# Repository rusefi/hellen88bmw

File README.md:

# Team

Product Owner @StefanSt

[Issue Tracker](https://github.com/rusefi/hellen88bmw-issues)

[User documentation](https://rusefi.com/s/hellen88bmw)

Part of https://github.com/andreika-git/hellen-one family

Inspired by https://github.com/rusefi/hw_88_bmw

# compatible cases

0260002360 TCU yes or no?

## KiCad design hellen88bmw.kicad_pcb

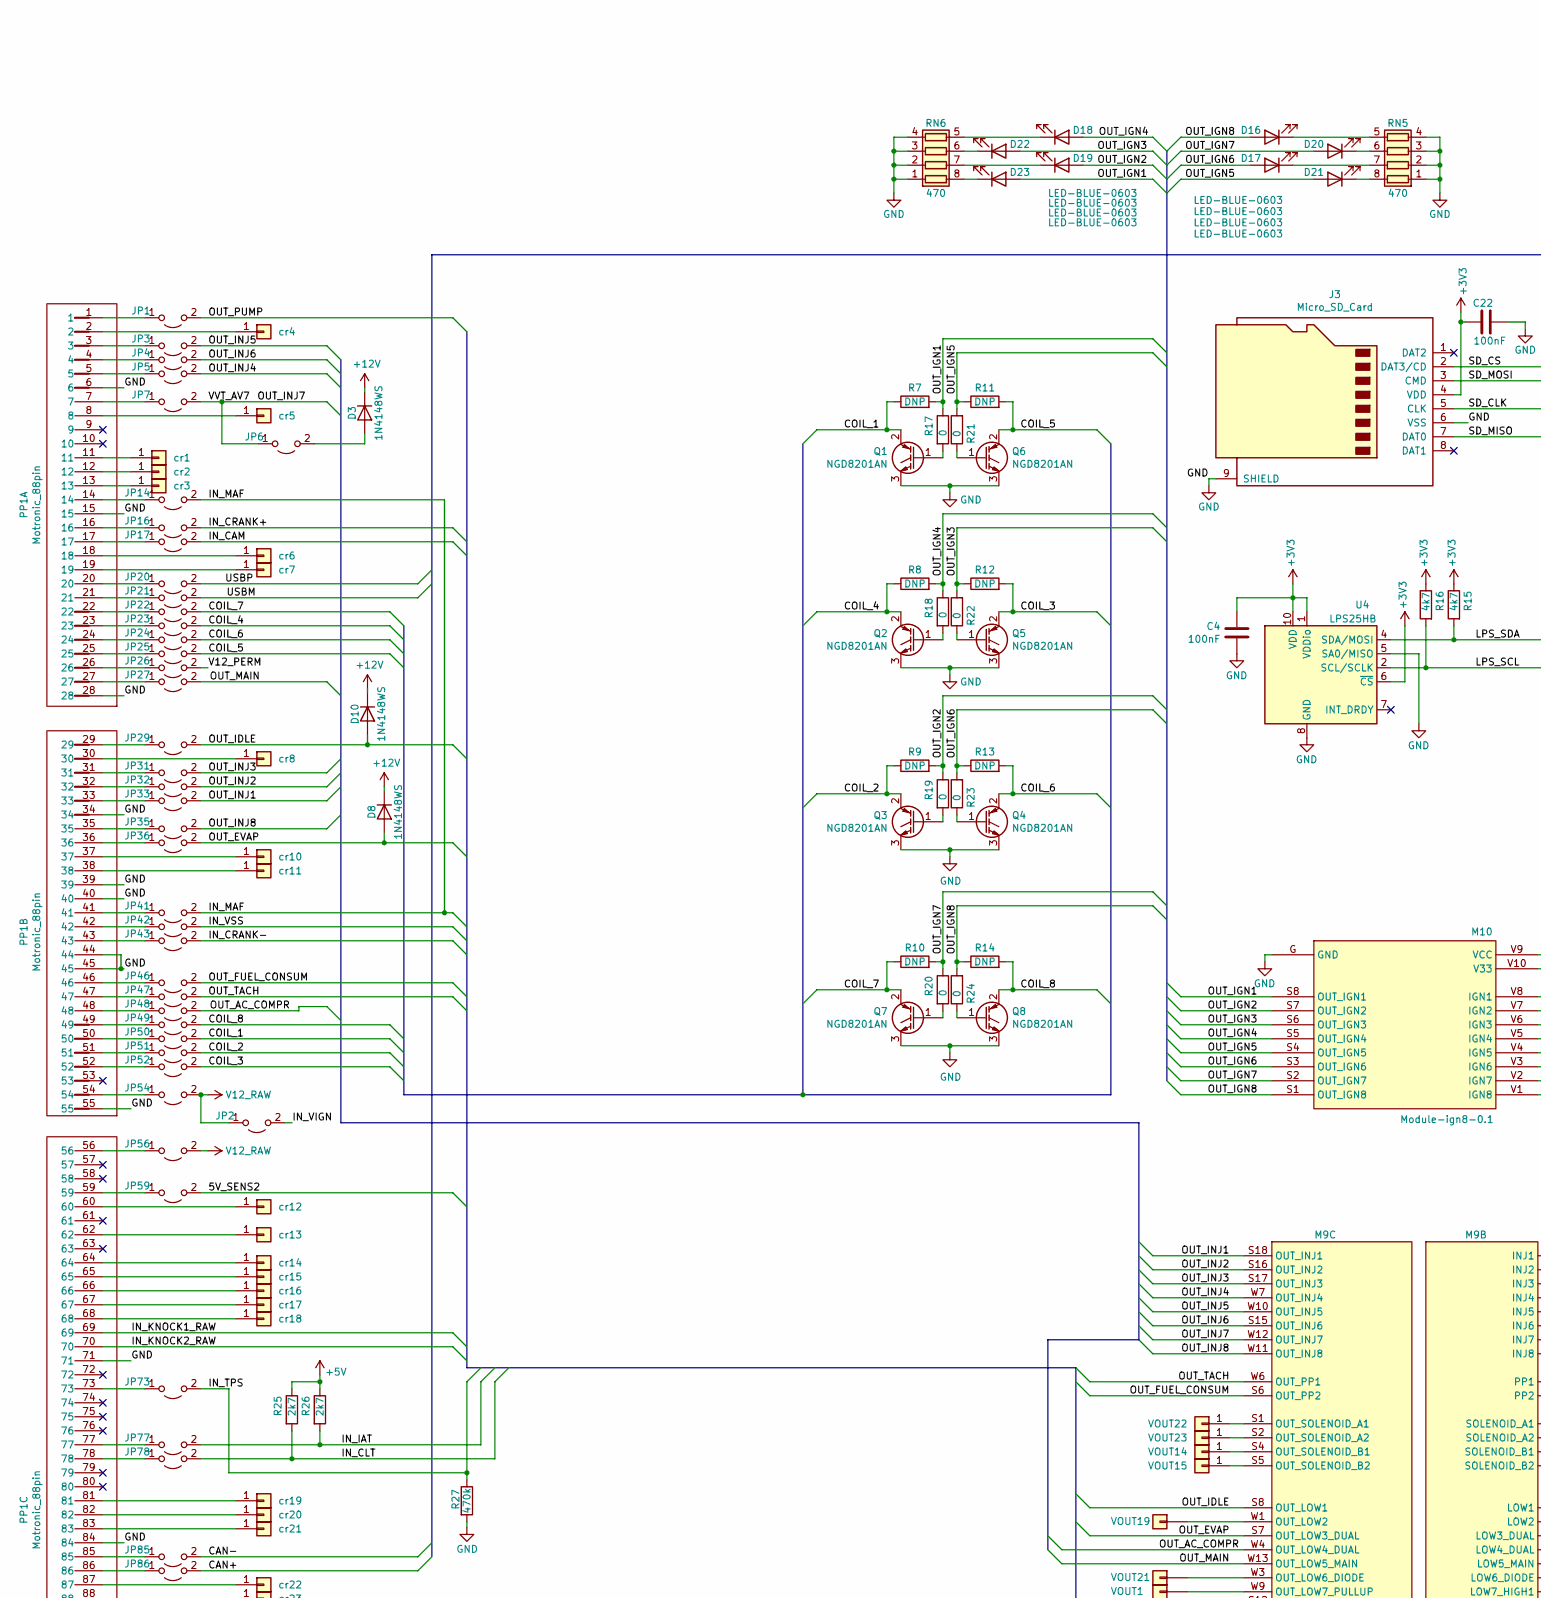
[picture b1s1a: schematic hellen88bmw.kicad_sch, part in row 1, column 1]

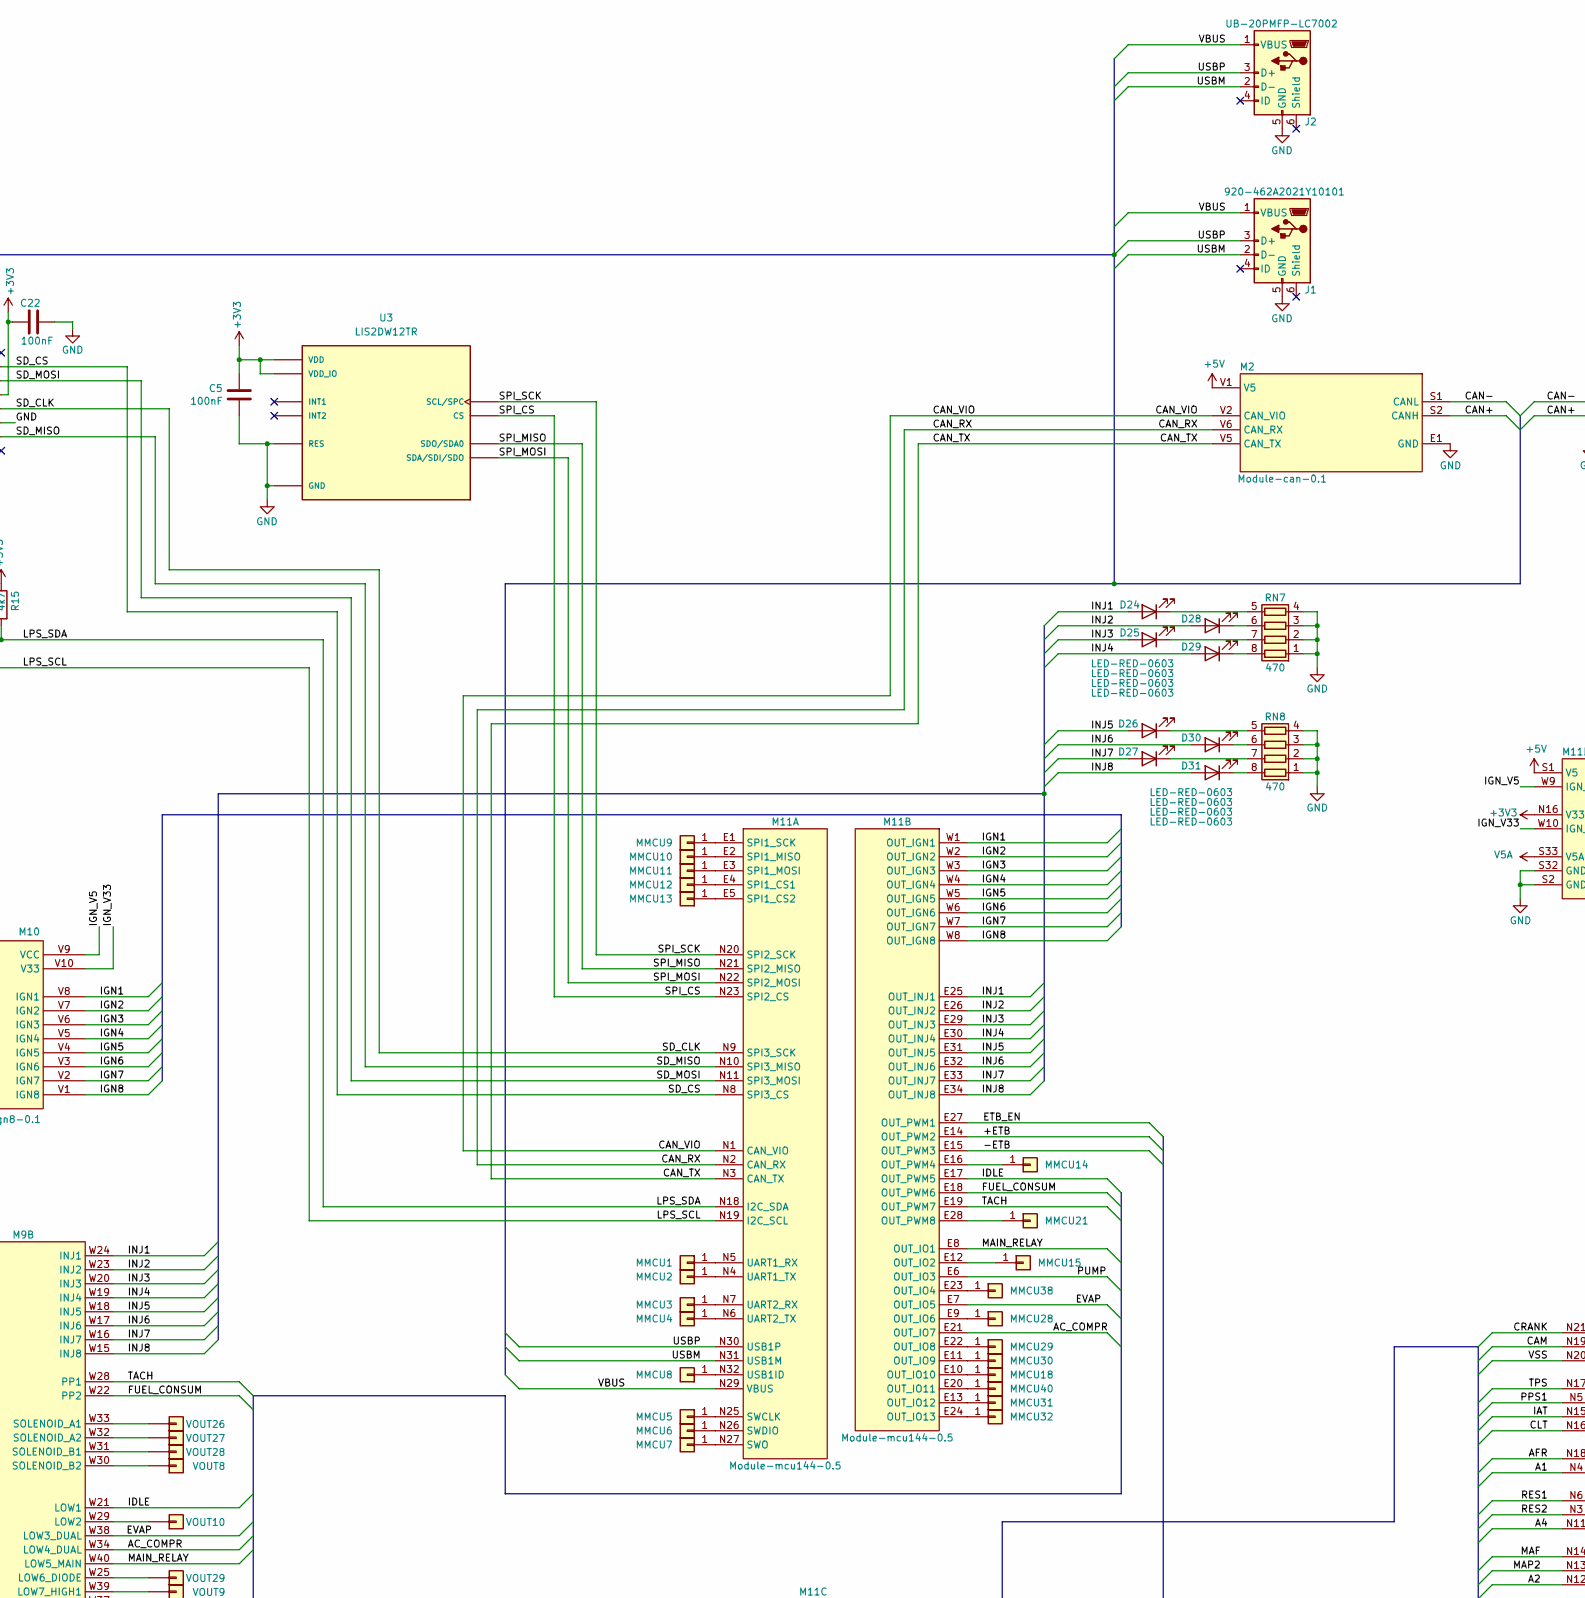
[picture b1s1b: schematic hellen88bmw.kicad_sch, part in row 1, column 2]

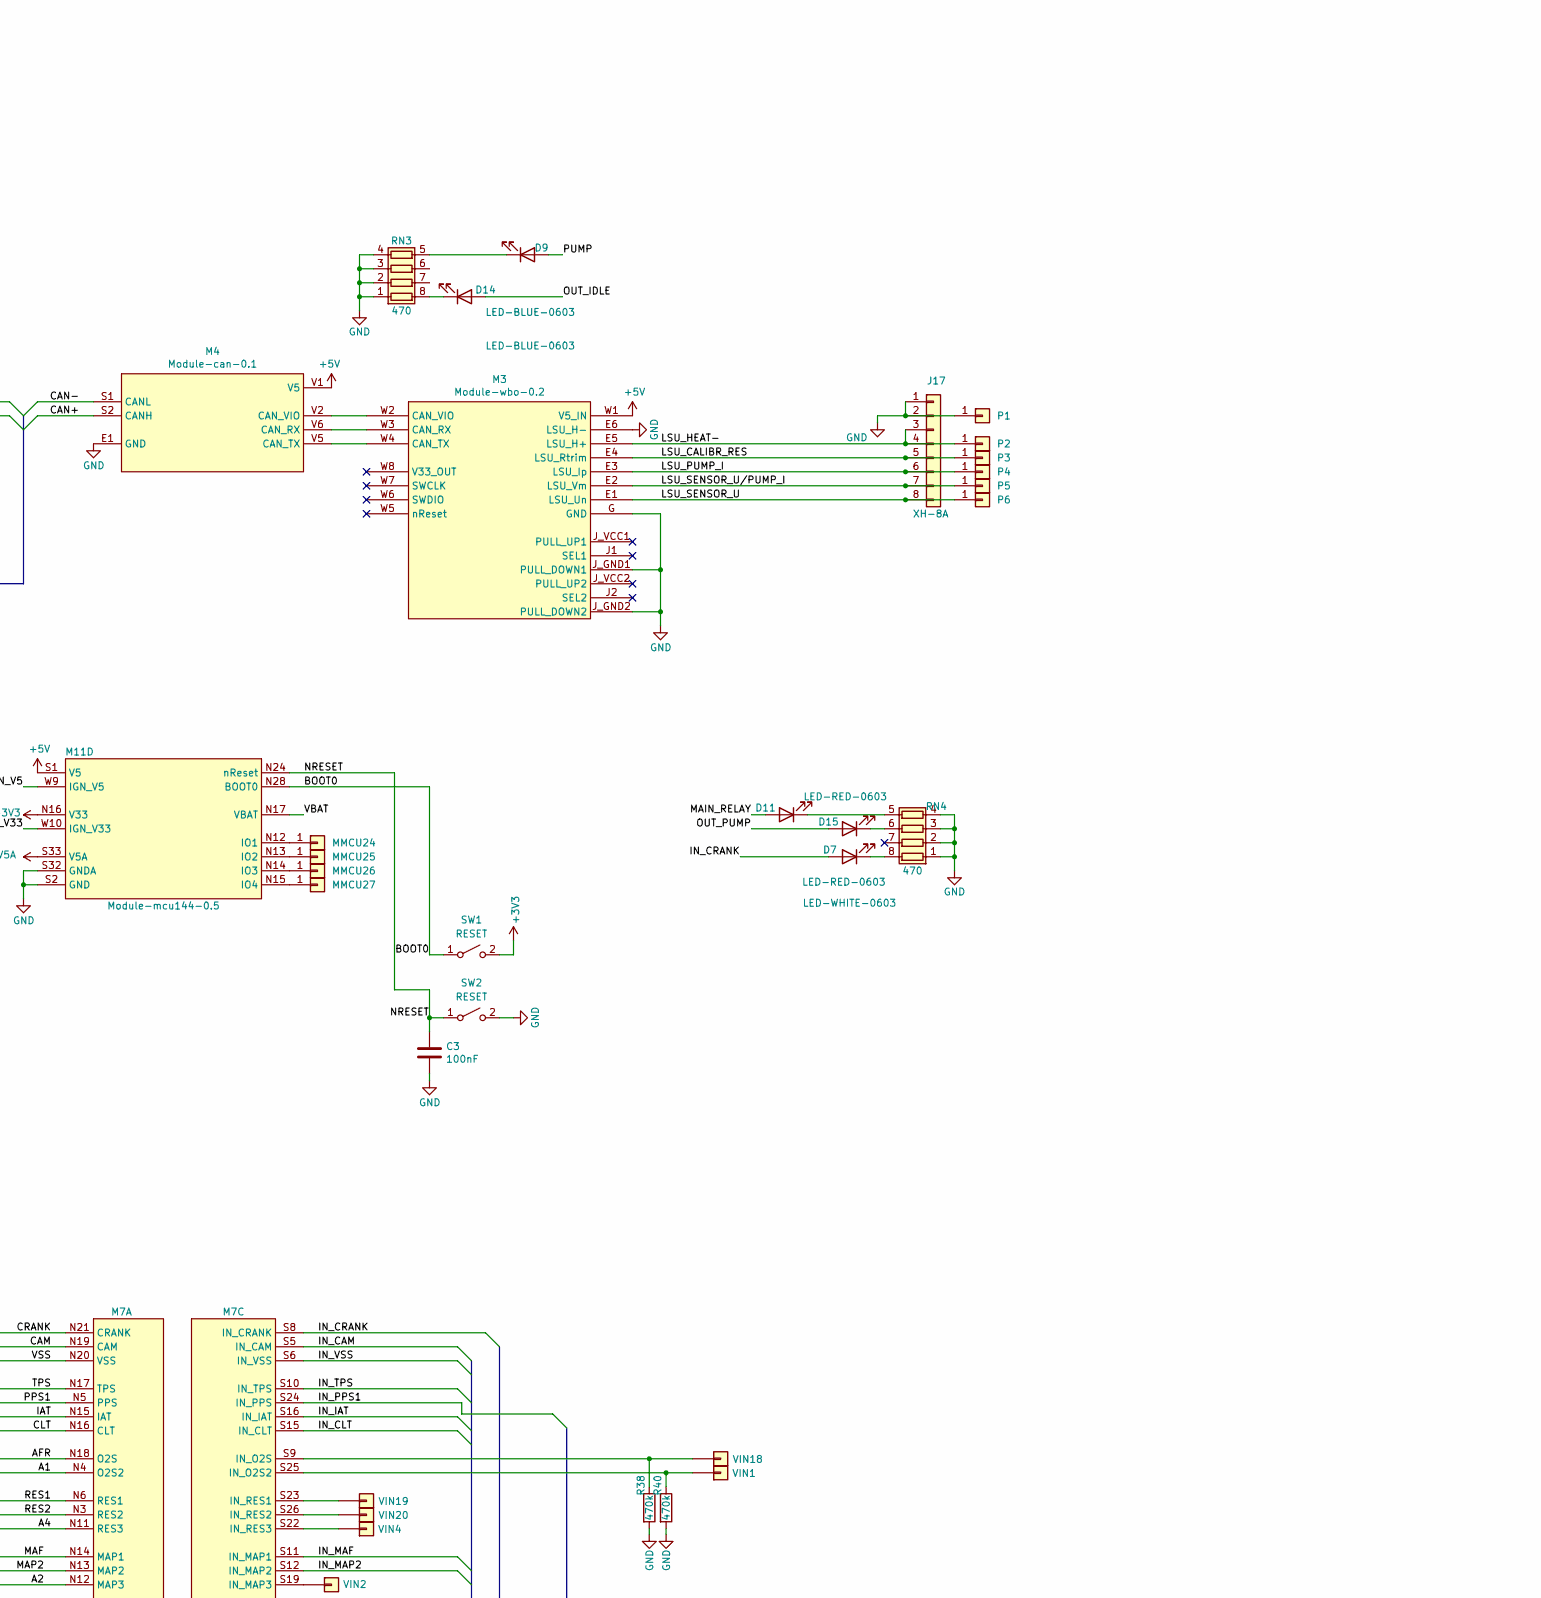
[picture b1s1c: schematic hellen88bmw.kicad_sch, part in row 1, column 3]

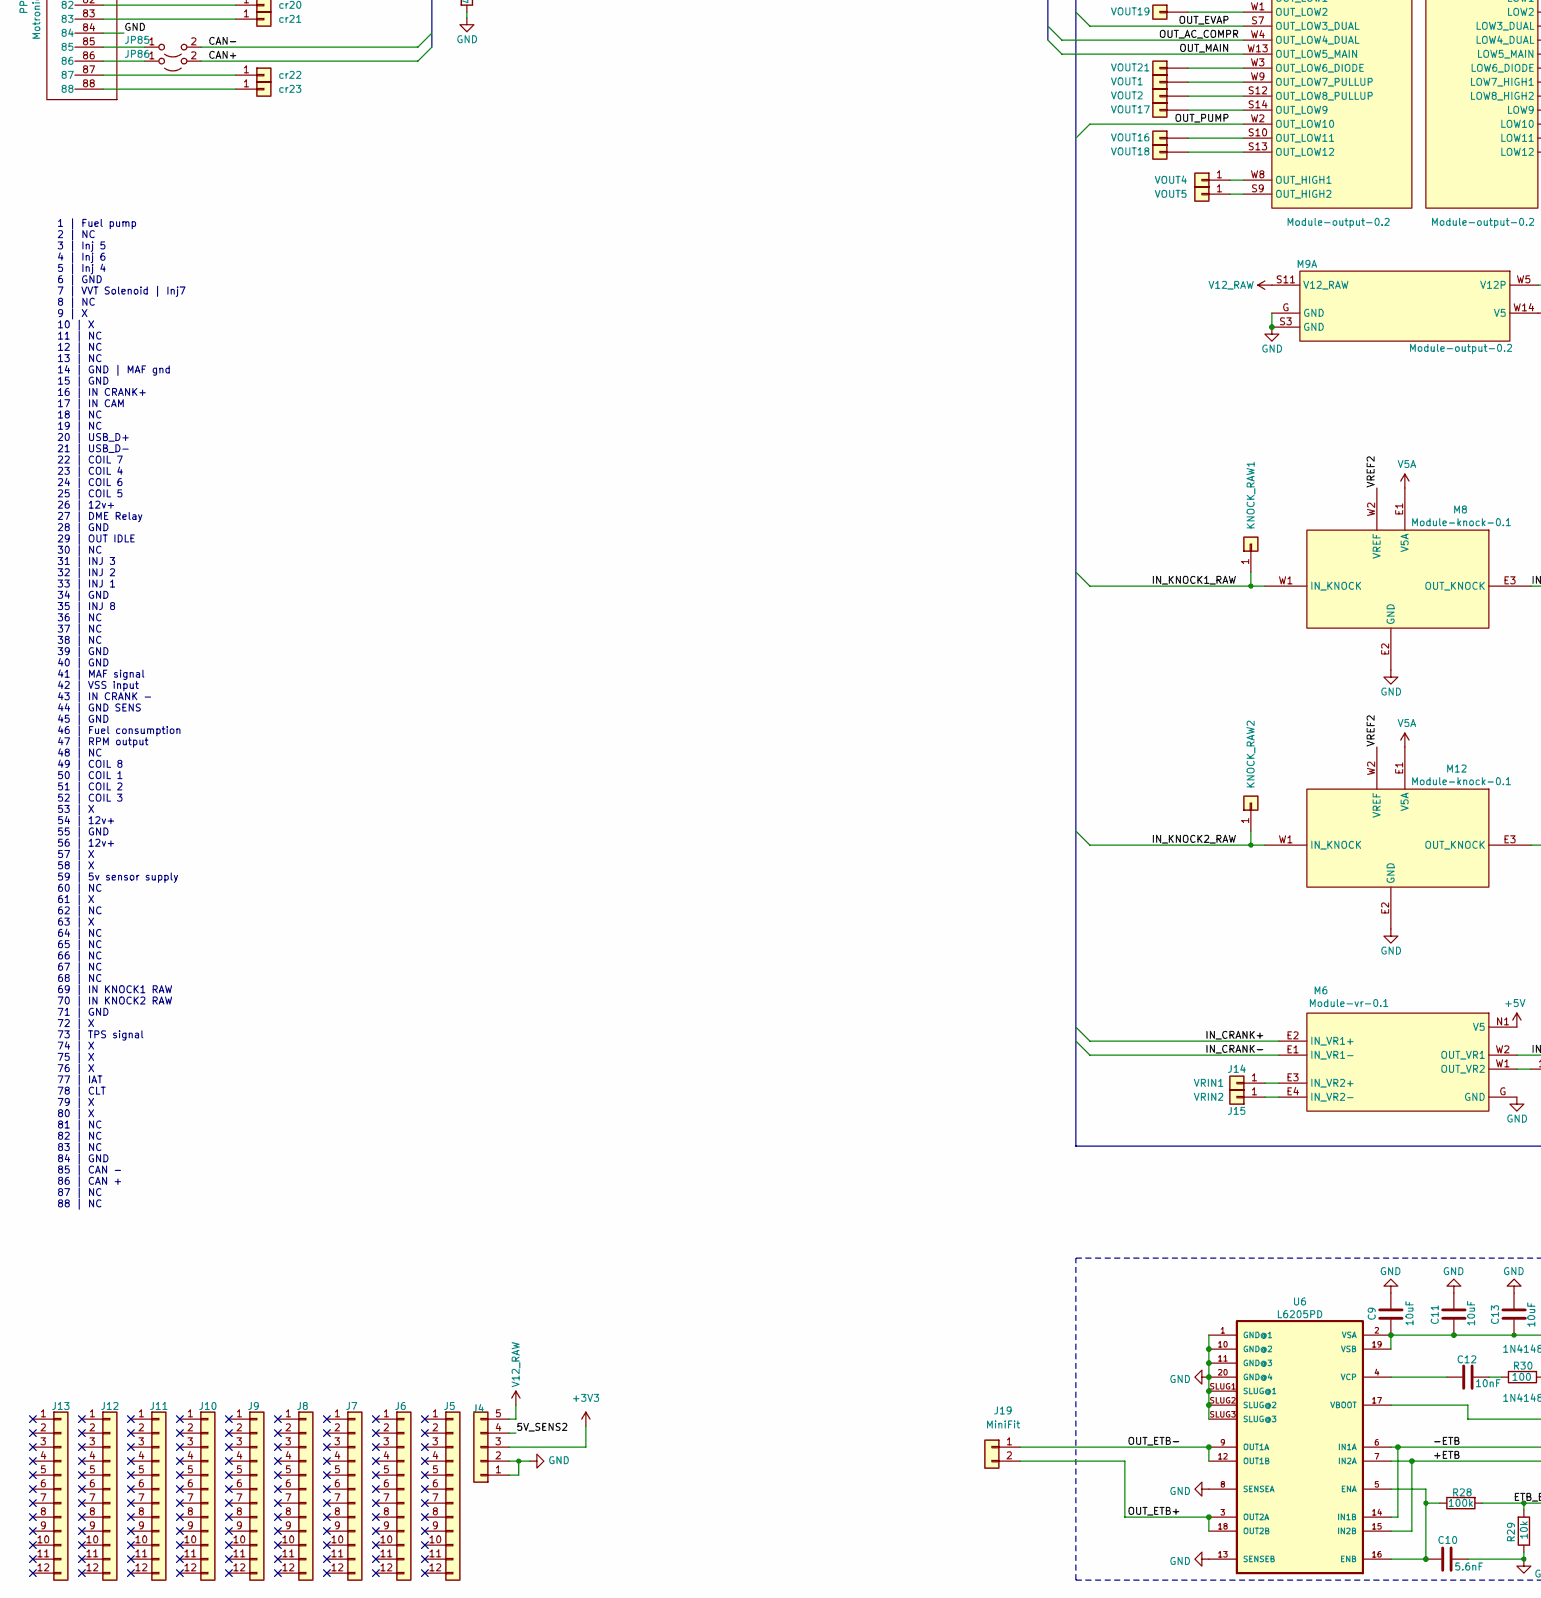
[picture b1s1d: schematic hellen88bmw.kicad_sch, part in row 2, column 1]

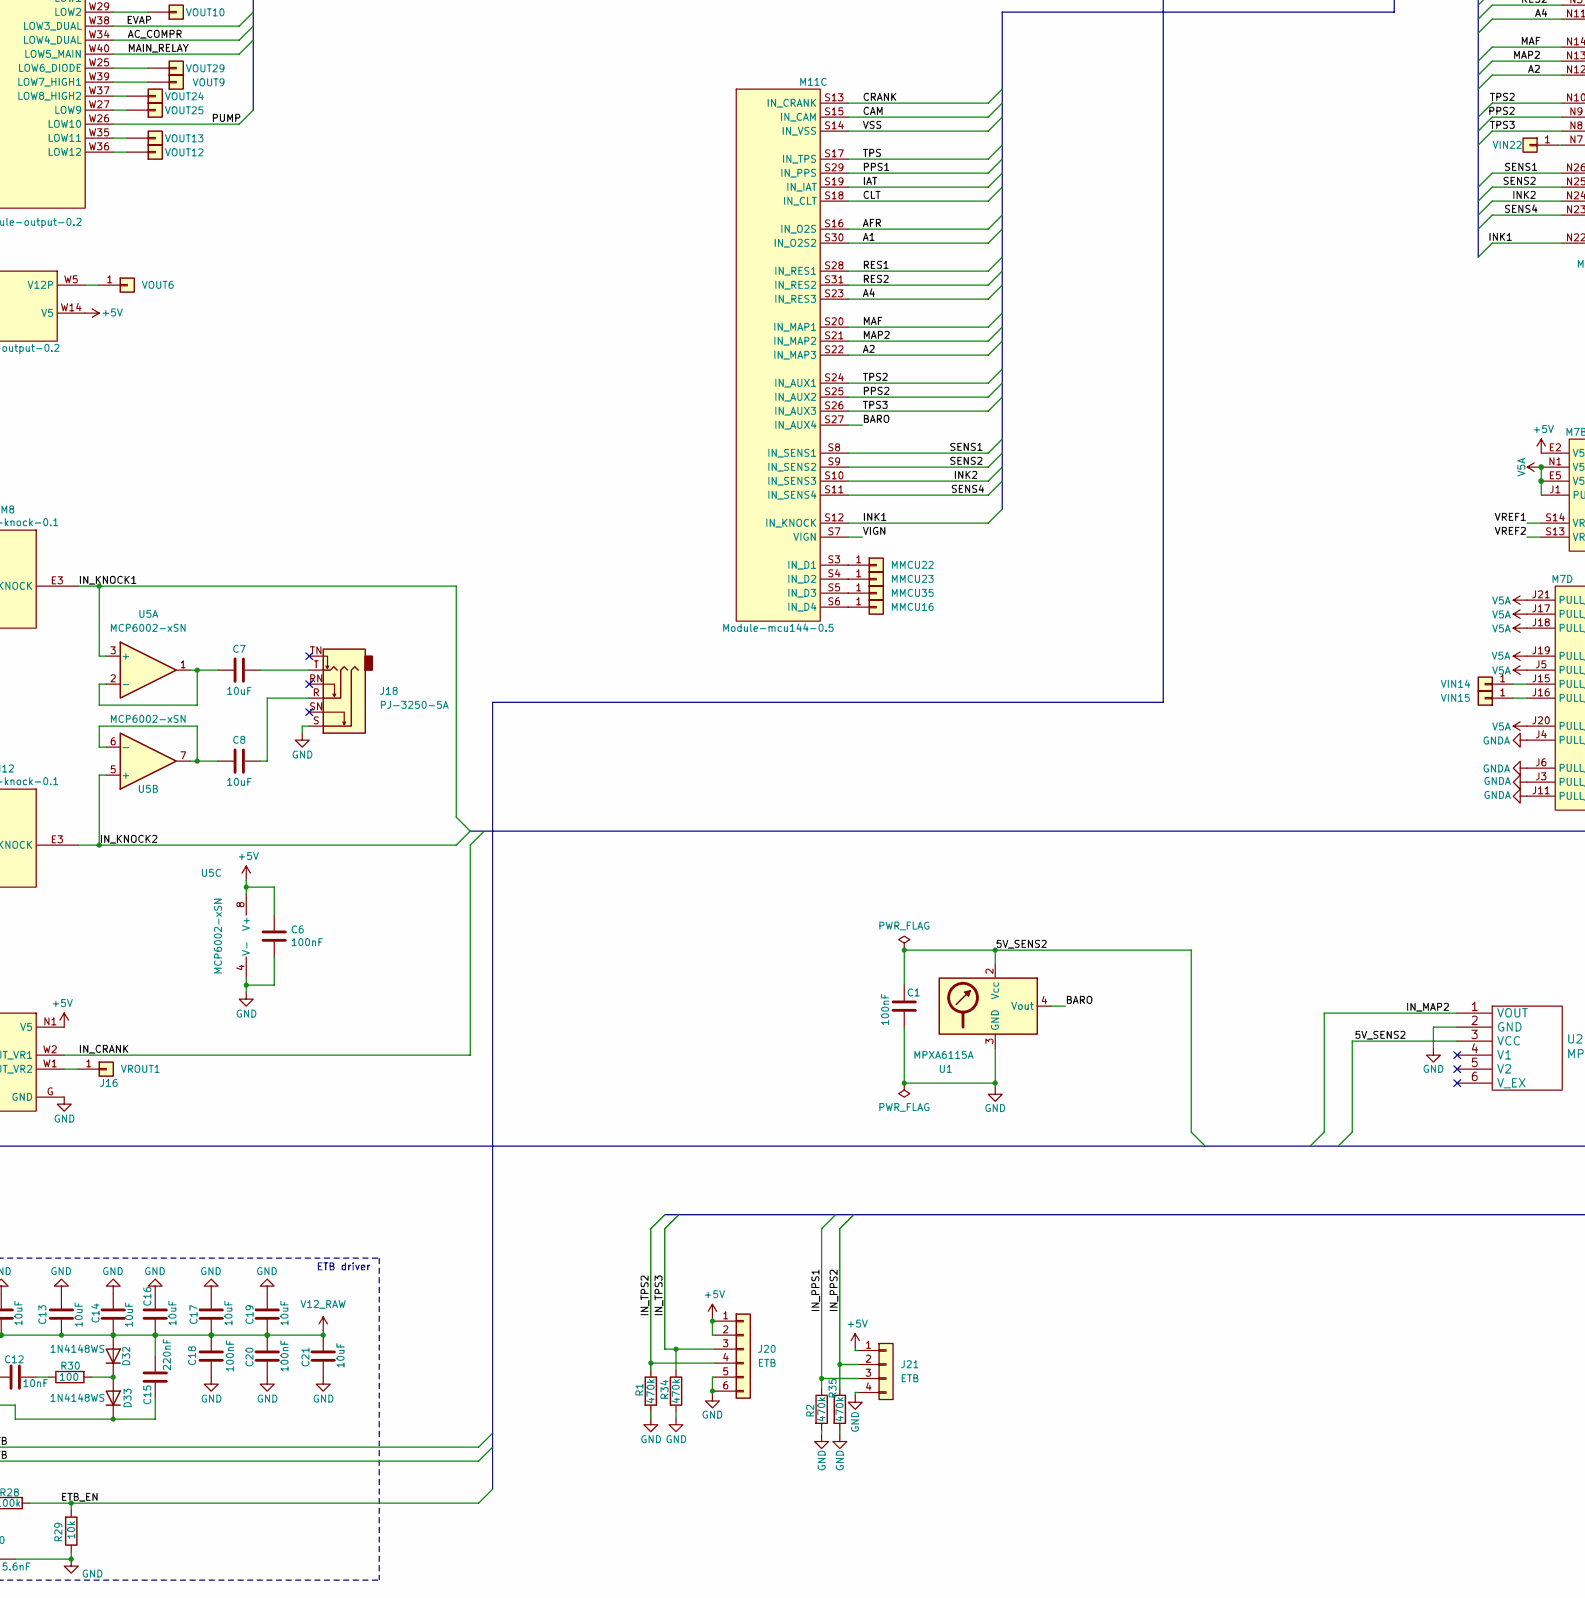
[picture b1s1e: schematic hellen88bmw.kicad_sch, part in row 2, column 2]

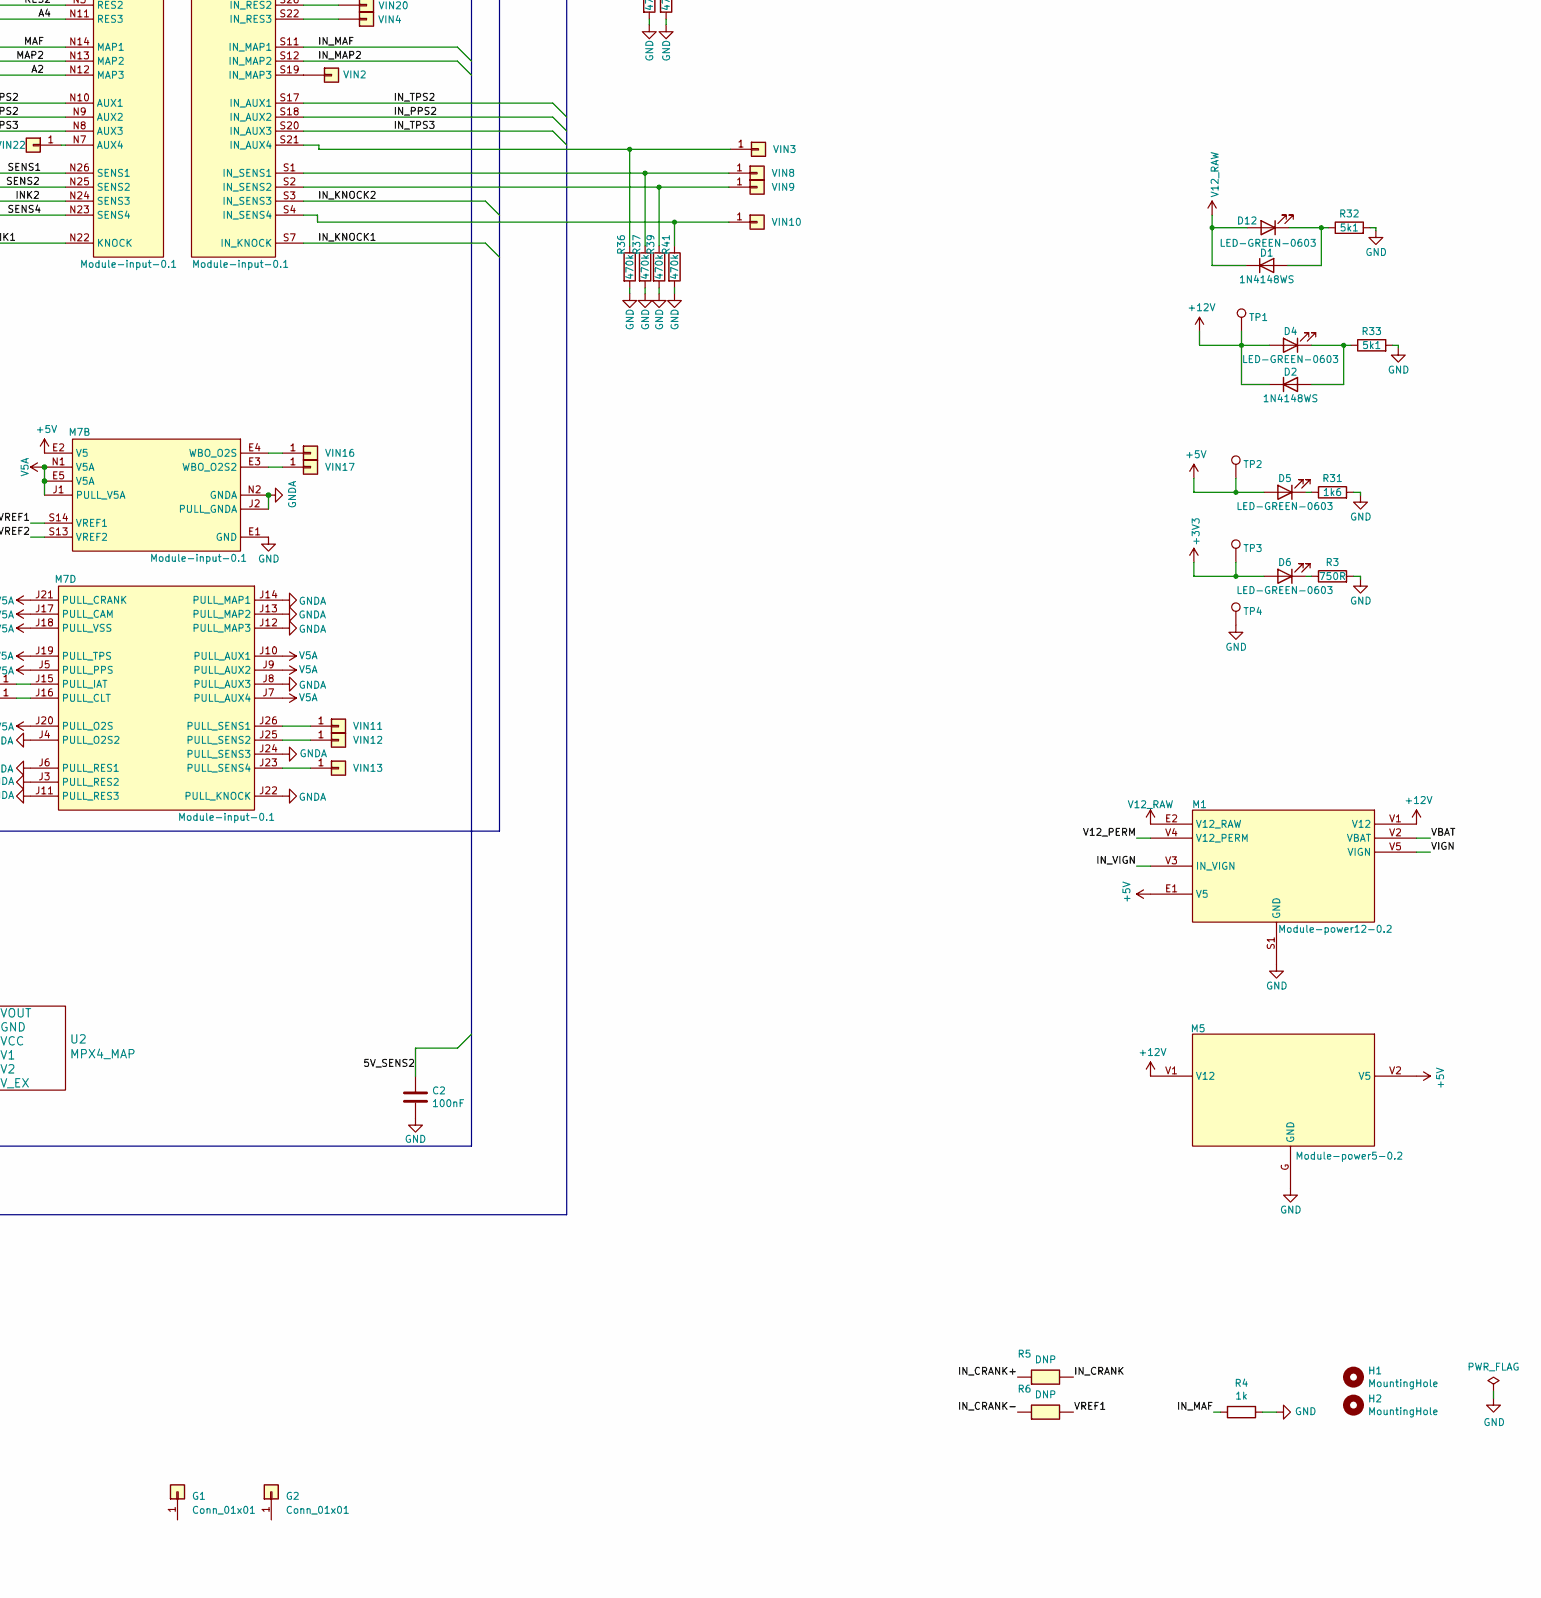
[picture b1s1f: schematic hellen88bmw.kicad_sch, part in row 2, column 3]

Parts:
C1, C2, C3, C4, C5, C6, C18, C20, C22: 100nF; C_0402_1005Metric; LCSC C105882
C7, C8, C9, C11, C13, C14, C16, C17, C19, C21: 10uF; C_0603_1608Metric; LCSC C87152
C10: 5.6nF; C_0402_1005Metric; LCSC C115688
C12: 10nF; C_0402_1005Metric; LCSC C541443
C15: 220nF; C_0402_1005Metric; LCSC C106258
D1, D2, D3, D8, D10, D32, D33: 1N4148WS; D_SOD-323; LCSC C2128
D4, D5, D6, D12: LED-GREEN-0603; LED_0603_1608Metric; LCSC C72043
D7: LED-WHITE-0603; LED_0603_1608Metric; LCSC C84265
D9, D14, D16, D17, D18, D19, D20, D21, D22, D23: LED-BLUE-0603; LED_0603_1608Metric; LCSC C72041
D11, D15, D24, D25, D26, D27, D28, D29, D30, D31: LED-RED-0603; LED_0603_1608Metric; LCSC C2286
G1, G2: Conn_01x01; LOGO
H1, H2: MountingHole; MountingHole_4.3mm_M4_DIN965
J1: 920-462A2021Y10101; USB-MINI-B-VERTICAL; LCSC C13453
J2: UB-20PMFP-LC7002; PinHeader_1x05_P2.00mm_Vertical; LCSC DNP
J3: Micro_SD_Card; 693072010801
J4: Conn_01x05; PinHeader_1x05_P2.54mm_Vertical
J5, J6, J7, J8, J9, J10, J11, J12, J13: Conn_01x12; PinHeader_1x12_P2.54mm_Vertical
J14: VRIN1; PinHeader_1x01_P1.00mm_Vertical
J15: VRIN2; PinHeader_1x01_P1.00mm_Vertical
J16: VROUT1; PinHeader_1x01_P1.00mm_Vertical
J17: XH-8A; LCSC C10385
J18: PJ-3250-5A; Jack_3.5mm_CUI_SJ1-3535NG_Horizontal; LCSC C165947
J19: MiniFit; Molex_Mini-Fit_Jr_5569-02A2_2x01_P4.20mm_Horizontal
J20: ETB; PinHeader_1x06_P2.54mm_Vertical; LCSC C343639
J21: ETB; PinHeader_1x04_P2.54mm_Vertical; LCSC C343639
JP1, JP2, JP3, JP4, JP5, JP7, JP14, JP16, JP17, JP22, JP23, JP24, JP25, JP26, JP27, JP29, JP31, JP32, JP33, JP35, JP36, JP41, JP42, JP43, JP46, JP47, JP48, JP49, JP50, JP51, JP52, JP56, JP59, JP73, JP77, JP78, JP85, JP86: Jumper_2_Open; SM0805_jumper; LCSC C17477
JP6, JP20, JP21, JP54: Jumper_2_Open; SM0805_jumper; LCSC DNP
KNOCK_RAW1: IN_KNOCK1_RAW; PinHeader_1x01_P1.00mm_Vertical
KNOCK_RAW2: IN_KNOCK2_RAW; PinHeader_1x01_P1.00mm_Vertical
M1: Module-power12-0.2; power12
M2, M4: Module-can-0.1; can
M3: Module-wbo-0.2; wbo
M5: Module-power5-0.2; power5
M6: Module-vr-0.1; vr
M7: Module-input-0.1; input
M8, M12: Module-knock-0.1; knock
M9: Module-output-0.2; output
M10: Module-ign8-0.1; ign8
M11: Module-mcu144-0.5; mcu
MMCU1, MMCU2, MMCU3, MMCU4, MMCU5, MMCU6, MMCU7, MMCU8, MMCU9, MMCU10, MMCU11, MMCU12, MMCU13, MMCU14, MMCU15, MMCU16, MMCU18, MMCU21, MMCU22, MMCU23, MMCU24, MMCU25, MMCU26, MMCU27, MMCU28, MMCU29, MMCU30, MMCU31, MMCU32, MMCU35, MMCU38, MMCU40: MMCU; PinHeader_1x01_P1.00mm_Vertical
P1, P2, P3, P4, P5, P6: P; Pin_D1.0mm_L10.0mm
PP1: Motronic_88pin; 88pin_STS
Q1, Q2, Q3, Q4, Q5, Q6, Q7, Q8: NGD8201AN; TO-252-2; LCSC C151649
R1, R2, R27, R34, R35, R36, R37, R38, R39, R40, R41: 470k; R_0402_1005Metric
R3: 750R; R_0402_1005Metric
R4: 1k; R_0402_1005Metric; LCSC C105637
R5, R6: DNP; R_0402_1005Metric; LCSC NA
R7, R8, R9, R10, R11, R12, R13, R14: DNP; R_2512_6332Metric; LCSC NA
R15, R16: 4k7; R_0402_1005Metric; LCSC C163826
R17, R18, R19, R20, R21, R22, R23, R24: 0; R_0402_1005Metric; LCSC C106231
R25, R26: 2k7; R_0402_1005Metric; LCSC C138017
R28: 100k; R_0402_1005Metric; LCSC C106234
R29: 10k; R_0402_1005Metric; LCSC C60489
R30: 100; R_0402_1005Metric; LCSC C106233
R31: 1k6; R_0402_1005Metric
R32, R33: 5k1; R_0402_1005Metric
RN3, RN4, RN5, RN6, RN7, RN8: 470; R_Array_Concave_4x0603; LCSC C25510
SW1, SW2: RESET; SW_SPST_B3U-1000P-B; LCSC C231329
TP1, TP2, TP3, TP4: TestPoint; TestPoint_Pad_D1.0mm
U1: MPXA6115A; SSO-8_6.8x5.9mm_P1.27mm_Clearance7mm
U2: MPX4_MAP; MPX-4_MAP
U3: LIS2DW12TR; LGA12R50P4X4_200X200X70; PARTREV 4; LCSC C189624
U4: LPS25HB; ST_HLGA-10_2.5x2.5mm_P0.6mm_LayoutBorder3x2y; LCSC C87898
U5: MCP6002-xSN; SOIC-8_3.9x4.9mm_P1.27mm; LCSC C7377
U6: L6205PD; SO20POWER; LCSC C36543
VIN1, VIN2, VIN4, VIN18, VIN19, VIN20: Pad; PinHeader_1x01_P1.00mm_Vertical
VIN3, VIN8: VIN8; PinHeader_1x01_P1.00mm_Vertical
VIN9: VIN9; PinHeader_1x01_P1.00mm_Vertical
VIN10: VIN10; PinHeader_1x01_P1.00mm_Vertical
VIN11: VIN11; PinHeader_1x01_P1.00mm_Vertical
VIN12: VIN12; PinHeader_1x01_P1.00mm_Vertical
VIN13: VIN13; PinHeader_1x01_P1.00mm_Vertical
VIN14: VIN14; PinHeader_1x01_P1.00mm_Vertical
VIN15: VIN15; PinHeader_1x01_P1.00mm_Vertical
VIN16: VIN16; PinHeader_1x01_P1.00mm_Vertical
VIN17: VIN17; PinHeader_1x01_P1.00mm_Vertical
VIN22: VIN5; PinHeader_1x01_P1.00mm_Vertical
VOUT1, VOUT2, VOUT8, VOUT9, VOUT10, VOUT12, VOUT13, VOUT16, VOUT17, VOUT18, VOUT19, VOUT21, VOUT24, VOUT25, VOUT26, VOUT27, VOUT28, VOUT29: Pad; PinHeader_1x01_P1.00mm_Vertical
VOUT4, VOUT14, VOUT15, VOUT22, VOUT23: VOUT4; PinHeader_1x01_P1.00mm_Vertical
VOUT5: VOUT5; PinHeader_1x01_P1.00mm_Vertical
VOUT6: VOUT6; PinHeader_1x01_P1.00mm_Vertical
cr1, cr2, cr3, cr4, cr5, cr6, cr7, cr8, cr10, cr11, cr12, cr13, cr14, cr15, cr16, cr17, cr18, cr19, cr20, cr21, cr22, cr23: cr; PinHeader_1x01_P1.00mm_Vertical

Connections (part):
+3V3: C4.1, C5.1, C22.1, D6.2 (A), J3.4 (VDD), J4.3, M11.N16 (V33), R15.1, R16.1, SW1.2 (B), TP3.1, U3.9 (VDD), U3.10 (VDD_IO), U4.1 (VDDio), U4.6 (~CS), U4.10 (VDD)
+5V: C6.1, D5.2 (A), J20.1, J20.2, J21.1, M1.E1 (V5), M2.V1 (V5), M3.W1 (V5_IN), M4.V1 (V5), M5.V2 (V5), M6.N1 (V5), M7.E2 (V5), M9.W14 (V5), M11.S1 (V5), R25.1, R26.1, TP2.1, U5.8 (V+)
+12V: D2.1 (K), D3.1 (K), D4.2 (A), D8.1 (K), D10.1 (K), M1.V1 (V12), M5.V1 (V12), TP1.1
/5V_SENS2: C1.1, C2.1, J4.4, JP59.2 (B), U1.2 (Vcc), U2.3 (VCC)
/+ETB: M11.E14 (OUT_PWM2), U6.7 (IN2A), U6.15 (IN2B)
/-ETB: M11.E15 (OUT_PWM3), U6.6 (IN1A), U6.14 (IN1B)
/A1: M7.N4 (O2S2), M11.S30 (IN_O2S2)
/A2: M7.N12 (MAP3), M11.S22 (IN_MAP3)
/A4: M7.N11 (RES3), M11.S23 (IN_RES3)
/AC_COMPR: M9.W34 (LOW4_DUAL), M11.E21 (OUT_IO7)
/AFR: M7.N18 (O2S), M11.S16 (IN_O2S)
/BARO: M11.S27 (IN_AUX4), U1.4 (Vout)
/BOOT0: M11.N28 (BOOT0), SW1.1 (A)
/CAM: M7.N19 (CAM), M11.S15 (IN_CAM)
/CAN+: JP86.2 (B), M2.S2 (CANH), M4.S2 (CANH)
/CAN-: JP85.2 (B), M2.S1 (CANL), M4.S1 (CANL)
/CAN_RX: M2.V6 (CAN_RX), M11.N2 (CAN_RX)
/CAN_TX: M2.V5 (CAN_TX), M11.N3 (CAN_TX)
/CAN_VIO: M2.V2 (CAN_VIO), M11.N1 (CAN_VIO)
/CLT: M7.N16 (CLT), M11.S18 (IN_CLT)
/COIL_1: JP50.2 (B), Q1.2 (C), R7.1
/COIL_2: JP51.2 (B), Q3.2 (C), R9.1
/COIL_3: JP52.2 (B), Q5.2 (C), R12.2
/COIL_4: JP23.2 (B), Q2.2 (C), R8.1
/COIL_5: JP25.2 (B), Q6.2 (C), R11.2
/COIL_6: JP24.2 (B), Q4.2 (C), R13.2
/COIL_7: JP22.2 (B), Q7.2 (C), R10.1
/COIL_8: JP49.2 (B), Q8.2 (C), R14.2
/CRANK: M7.N21 (CRANK), M11.S13 (IN_CRANK)
/ETB_EN: M11.E27 (OUT_PWM1), R28.2, R29.2
/EVAP: M9.W38 (LOW3_DUAL), M11.E7 (OUT_IO5)
/FUEL_CONSUM: M9.W22 (PP2), M11.E18 (OUT_PWM6)
/IAT: M7.N15 (IAT), M11.S19 (IN_IAT)
/IDLE: M9.W21 (LOW1), M11.E17 (OUT_PWM5)
/IGN1: M10.V8 (IGN1), M11.W1 (OUT_IGN1)
/IGN2: M10.V7 (IGN2), M11.W2 (OUT_IGN2)
/IGN3: M10.V6 (IGN3), M11.W3 (OUT_IGN3)
/IGN4: M10.V5 (IGN4), M11.W4 (OUT_IGN4)
/IGN5: M10.V4 (IGN5), M11.W5 (OUT_IGN5)
/IGN6: M10.V3 (IGN6), M11.W6 (OUT_IGN6)
/IGN7: M10.V2 (IGN7), M11.W7 (OUT_IGN7)
/IGN8: M10.V1 (IGN8), M11.W8 (OUT_IGN8)
/IGN_V5: M10.V9 (VCC), M11.W9 (IGN_V5)
/IGN_V33: M10.V10 (V33), M11.W10 (IGN_V33)
/INJ1: D24.2 (A), M9.W24 (INJ1), M11.E25 (OUT_INJ1)
/INJ2: D28.2 (A), M9.W23 (INJ2), M11.E26 (OUT_INJ2)
/INJ3: D25.2 (A), M9.W20 (INJ3), M11.E29 (OUT_INJ3)
/INJ4: D29.2 (A), M9.W19 (INJ4), M11.E30 (OUT_INJ4)
/INJ5: D26.2 (A), M9.W18 (INJ5), M11.E31 (OUT_INJ5)
/INJ6: D30.2 (A), M9.W17 (INJ6), M11.E32 (OUT_INJ6)
/INJ7: D27.2 (A), M9.W16 (INJ7), M11.E33 (OUT_INJ7)
/INJ8: D31.2 (A), M9.W15 (INJ8), M11.E34 (OUT_INJ8)
/INK1: M7.N22 (KNOCK), M11.S12 (IN_KNOCK)
/INK2: M7.N24 (SENS3), M11.S10 (IN_SENS3)
/IN_CAM: JP17.2 (B), M7.S5 (IN_CAM)
/IN_CLT: JP78.2 (B), M7.S15 (IN_CLT), R25.2
/IN_CRANK: D7.2 (A), M6.W2 (OUT_VR1), M7.S8 (IN_CRANK), R5.2
/IN_CRANK+: JP16.2 (B), M6.E2 (IN_VR1+), R5.1
/IN_CRANK-: JP43.2 (B), M6.E1 (IN_VR1-), R6.1
/IN_IAT: JP77.2 (B), M7.S16 (IN_IAT), R26.2
/IN_KNOCK1: M7.S7 (IN_KNOCK), M8.E3 (OUT_KNOCK), U5.3 (+)
/IN_KNOCK1_RAW: KNOCK_RAW1.1, M8.W1 (IN_KNOCK), PP1.69
/IN_KNOCK2: M7.S3 (IN_SENS3), M12.E3 (OUT_KNOCK), U5.5 (+)
/IN_KNOCK2_RAW: KNOCK_RAW2.1, M12.W1 (IN_KNOCK), PP1.70
/IN_MAF: JP14.2 (B), JP41.2 (B), M7.S11 (IN_MAP1), R4.2
/IN_MAP2: M7.S12 (IN_MAP2), U2.1 (VOUT)
/IN_PPS1: J21.3, M7.S24 (IN_PPS), R2.1
/IN_PPS2: J21.2, M7.S18 (IN_AUX2), R35.1
/IN_TPS: JP73.2 (B), M7.S10 (IN_TPS), R27.1
/IN_TPS2: J20.4, M7.S17 (IN_AUX1), R1.1
/IN_TPS3: J20.3, M7.S20 (IN_AUX3), R34.1
/IN_VIGN: JP2.2 (B), M1.V3 (IN_VIGN)
/IN_VSS: JP42.2 (B), M7.S6 (IN_VSS)
/LPS_SCL: M11.N19 (I2C_SCL), R16.2, U4.2 (SCL/SCLK)
/LPS_SDA: M11.N18 (I2C_SDA), R15.2, U4.4 (SDA/MOSI)
/LSU_CALIBR_RES: J17.5, M3.E4 (LSU_Rtrim), P3.1
/LSU_HEAT-: J17.3, J17.4, M3.E5 (LSU_H+), P2.1
/LSU_PUMP_I: J17.6, M3.E3 (LSU_Ip), P4.1
/LSU_SENSOR_U: J17.8, M3.E1 (LSU_Un), P6.1
/LSU_SENSOR_U/PUMP_I: J17.7, M3.E2 (LSU_Vm), P5.1
/MAF: M7.N14 (MAP1), M11.S20 (IN_MAP1)
/MAIN_RELAY: D11.2 (A), M9.W40 (LOW5_MAIN), M11.E8 (OUT_IO1)
/MAP2: M7.N13 (MAP2), M11.S21 (IN_MAP2)
/NRESET: C3.1, M11.N24 (nReset), SW2.1 (A)
/OUT_AC_COMPR: JP48.2 (B), M9.W4 (OUT_LOW4_DUAL)
/OUT_ETB+: J19.2, U6.3 (OUT2A), U6.18 (OUT2B)
/OUT_ETB-: J19.1, U6.9 (OUT1A), U6.12 (OUT1B)
/OUT_EVAP: D8.2 (A), JP36.2 (B), M9.S7 (OUT_LOW3_DUAL)
/OUT_FUEL_CONSUM: JP46.2 (B), M9.S6 (OUT_PP2)
/OUT_IDLE: D10.2 (A), D14.2 (A), JP29.2 (B), M9.S8 (OUT_LOW1)
/OUT_IGN1: D23.2 (A), M10.S8 (OUT_IGN1), R7.2, R17.1
/OUT_IGN2: D19.2 (A), M10.S7 (OUT_IGN2), R9.2, R19.1
/OUT_IGN3: D22.2 (A), M10.S6 (OUT_IGN3), R12.1, R22.2
/OUT_IGN4: D18.2 (A), M10.S5 (OUT_IGN4), R8.2, R18.1
/OUT_IGN5: D21.2 (A), M10.S4 (OUT_IGN5), R11.1, R21.2
/OUT_IGN6: D17.2 (A), M10.S3 (OUT_IGN6), R13.1, R23.2
/OUT_IGN7: D20.2 (A), M10.S2 (OUT_IGN7), R10.2, R20.1
/OUT_IGN8: D16.2 (A), M10.S1 (OUT_IGN8), R14.1, R24.2
/OUT_INJ1: JP33.2 (B), M9.S18 (OUT_INJ1)
/OUT_INJ2: JP32.2 (B), M9.S16 (OUT_INJ2)
/OUT_INJ3: JP31.2 (B), M9.S17 (OUT_INJ3)
/OUT_INJ4: JP5.2 (B), M9.W7 (OUT_INJ4)
/OUT_INJ5: JP3.2 (B), M9.W10 (OUT_INJ5)
/OUT_INJ6: JP4.2 (B), M9.S15 (OUT_INJ6)
/OUT_INJ7: JP6.1 (A), JP7.2 (B), M9.W12 (OUT_INJ7)
/OUT_INJ8: JP35.2 (B), M9.W11 (OUT_INJ8)
/OUT_MAIN: JP27.2 (B), M9.W13 (OUT_LOW5_MAIN)
/OUT_PUMP: D15.2 (A), JP1.2 (B), M9.W2 (OUT_LOW10)
/OUT_TACH: JP47.2 (B), M9.W6 (OUT_PP1)
/PPS1: M7.N5 (PPS), M11.S29 (IN_PPS)
/PPS2: M7.N9 (AUX2), M11.S25 (IN_AUX2)
/PUMP: D9.2 (A), M9.W26 (LOW10), M11.E6 (OUT_IO3)
/RES1: M7.N6 (RES1), M11.S28 (IN_RES1)
/RES2: M7.N3 (RES2), M11.S31 (IN_RES2)
/SD_CLK: J3.5 (CLK), M11.N9 (SPI3_SCK)
/SD_CS: J3.2 (DAT3/CD), M11.N8 (SPI3_CS)
/SD_MISO: J3.7 (DAT0), M11.N10 (SPI3_MISO)
/SD_MOSI: J3.3 (CMD), M11.N11 (SPI3_MOSI)
/SENS1: M7.N26 (SENS1), M11.S8 (IN_SENS1)
/SENS2: M7.N25 (SENS2), M11.S9 (IN_SENS2)
/SENS4: M7.N23 (SENS4), M11.S11 (IN_SENS4)
/SPI_CS: M11.N23 (SPI2_CS), U3.2 (CS)
/SPI_MISO: M11.N21 (SPI2_MISO), U3.3 (SDO/SDA0)
/SPI_MOSI: M11.N22 (SPI2_MOSI), U3.4 (SDA/SDI/SDO)
/SPI_SCK: M11.N20 (SPI2_SCK), U3.1 (SCL/SPC)
/TACH: M9.W28 (PP1), M11.E19 (OUT_PWM7)
/TPS: M7.N17 (TPS), M11.S17 (IN_TPS)
/TPS2: M7.N10 (AUX1), M11.S24 (IN_AUX1)
/TPS3: M7.N8 (AUX3), M11.S26 (IN_AUX3)
/USBM: J1.2 (D-), J2.2 (D-), JP21.2 (B), M11.N31 (USB1M)
/USBP: J1.3 (D+), J2.3 (D+), JP20.2 (B), M11.N30 (USB1P)
/V12_PERM: JP26.2 (B), M1.V4 (V12_PERM)
/VBAT: M1.V2 (VBAT), M11.N17 (VBAT)
/VBUS: J1.1 (VBUS), J2.1 (VBUS), M11.N29 (VBUS)
/VIGN: M1.V5 (VIGN), M11.S7 (VIGN)
/VREF1: M7.S14 (VREF1), R6.2
/VREF2: M7.S13 (VREF2), M8.W2 (VREF), M12.W2 (VREF)
/VSS: M7.N20 (VSS), M11.S14 (IN_VSS)
GND: C1.2, C2.2, C3.2, C4.2, C5.2, C6.2, C9.2, C10.2, C11.2, C13.2, C14.2, C16.2, C17.2, C18.2, C19.2, C20.2, C21.2, C22.2, J1.5 (GND), J2.5 (GND), J3.6 (VSS), J3.9 (SHIELD), J4.1, J4.2, J17.1, J17.2, J18.S, J20.5, J20.6, J21.4, M1.S1 (GND), M2.E1 (GND), M3.E6 (LSU_H-), M3.G (GND), M3.J_GND1 (PULL_DOWN1), M3.J_GND2 (PULL_DOWN2), M4.E1 (GND), M5.G (GND), M6.G (GND), M7.E1 (GND), M8.E2 (GND), M9.G (GND), M9.S3 (GND), M10.G (GND), M11.S2 (GND), M11.S32 (GNDA), M12.E2 (GND), P1.1, PP1.6, PP1.15, PP1.28, PP1.34, PP1.39, PP1.40, PP1.44, PP1.45, PP1.55, PP1.71, PP1.84, Q1.3 (E), Q2.3 (E), Q3.3 (E), Q4.3 (E), Q5.3 (E), Q6.3 (E), Q7.3 (E), Q8.3 (E), R1.2, R2.2, R3.2, R4.1, R27.2, R29.1, R31.2, R32.2, R33.2, R34.2, R35.2, R36.2, R37.2, R38.2, R39.2, R40.2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
GNDA: M7.J2 (PULL_GNDA), M7.J3 (PULL_RES2), M7.J4 (PULL_O2S2), M7.J6 (PULL_RES1), M7.J8 (PULL_AUX3), M7.J11 (PULL_RES3), M7.J12 (PULL_MAP3), M7.J13 (PULL_MAP2), M7.J14 (PULL_MAP1), M7.J22 (PULL_KNOCK), M7.J24 (PULL_SENS3), M7.N2 (GNDA)
unnamed: C7.1, U5.1, U5.2 (-)
unnamed: C7.2, J18.T
unnamed: C8.1, U5.6 (-), U5.7
unnamed: C8.2, J18.R
unnamed: C10.1, R28.1, U6.5 (ENA), U6.16 (ENB)
unnamed: C12.1, R30.1
unnamed: C12.2, U6.4 (VCP)
unnamed: C15.2, D33.1 (K), U6.17 (VBOOT)
unnamed: D1.2 (A), D12.1 (K), R32.1
unnamed: D2.2 (A), D4.1 (K), R33.1
unnamed: D3.2 (A), JP6.2 (B)
unnamed: D5.1 (K), R31.1
unnamed: D6.1 (K), R3.1
unnamed: D7.1 (K), RN4.8 (R1.2)
unnamed: D9.1 (K), RN3.5 (R4.2)
unnamed: D11.1 (K), RN4.5 (R4.2)
unnamed: D14.1 (K), RN3.8 (R1.2)
unnamed: D15.1 (K), RN4.6 (R3.2)
unnamed: D16.1 (K), RN5.5 (R4.2)
unnamed: D17.1 (K), RN5.7 (R2.2)
unnamed: D18.1 (K), RN6.5 (R4.2)
unnamed: D19.1 (K), RN6.7 (R2.2)
unnamed: D20.1 (K), RN5.6 (R3.2)
unnamed: D21.1 (K), RN5.8 (R1.2)
unnamed: D22.1 (K), RN6.6 (R3.2)
unnamed: D23.1 (K), RN6.8 (R1.2)
unnamed: D24.1 (K), RN7.5 (R4.2)
unnamed: D25.1 (K), RN7.7 (R2.2)
unnamed: D26.1 (K), RN8.5 (R4.2)
unnamed: D27.1 (K), RN8.7 (R2.2)
unnamed: D28.1 (K), RN7.6 (R3.2)
unnamed: D29.1 (K), RN7.8 (R1.2)
unnamed: D30.1 (K), RN8.6 (R3.2)
unnamed: D31.1 (K), RN8.8 (R1.2)
unnamed: D32.1 (K), D33.2 (A), R30.2
unnamed: J14.1, M6.E3 (IN_VR2+)
unnamed: J15.1, M6.E4 (IN_VR2-)
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
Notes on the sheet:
1 | Fuel pump 2 | NC 3 | Inj 5 4 | Inj 6 5 | Inj 4 6 | GND 7 | VVT Solenoid | Inj7 8 | NC 9 | X 10 | X 11 | NC 12 | NC 13 | NC 14 | GND | MAF gnd 15 | GND 16 | IN CRANK+ 17 | IN CAM 18 | NC 19 | NC 20 | USB_D+ 21 | USB_D- 22 | COIL 7 23 | COIL 4 24 | COIL 6 25 | COIL 5 26 | 12v+ 27 | DME Relay 28 |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
ETB driver
